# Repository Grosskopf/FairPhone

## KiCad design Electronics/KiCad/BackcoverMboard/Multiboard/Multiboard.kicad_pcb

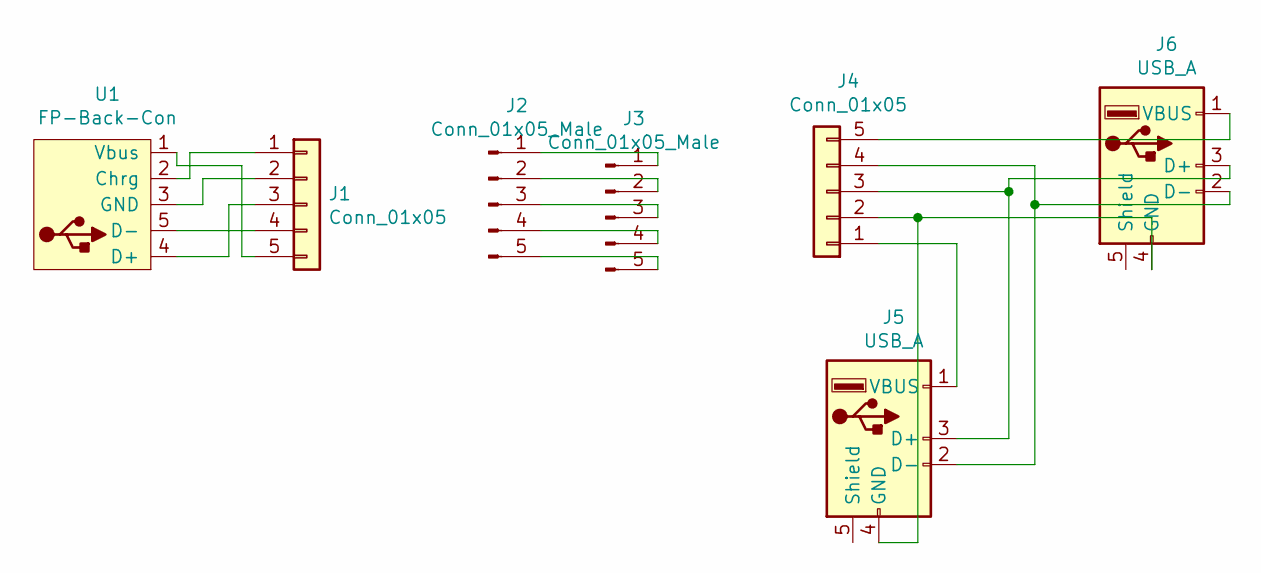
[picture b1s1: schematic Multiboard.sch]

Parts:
J1, J4: Conn_01x05; PinHeader_1x05_P2.54mm_Vertical
J2, J3: Conn_01x05_Male; Pad 01x05
J5: USB_A; usb-PCB
J6: USB_A; USB_A_Stewart_SS-52100-001_Horizontal
U1: FP-Back-Con; Fairphone-Back

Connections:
unnamed: J1.1, U1.2 (Chrg)
unnamed: J1.2, U1.3 (GND)
unnamed: J1.3, U1.4 (D+)
unnamed: J1.4, U1.5 (D-)
unnamed: J1.5, U1.1 (Vbus)
unnamed: J2.1, J3.1
unnamed: J2.2, J3.2
unnamed: J2.3, J3.3
unnamed: J2.4, J3.4
unnamed: J2.5, J3.5
unnamed: J4.1, J5.1 (VBUS)
unnamed: J4.2, J5.4 (GND), J6.4 (GND)
unnamed: J4.3, J5.3 (D+), J6.3 (D+)
unnamed: J4.4, J5.2 (D-), J6.2 (D-)
unnamed: J4.5, J6.1 (VBUS)

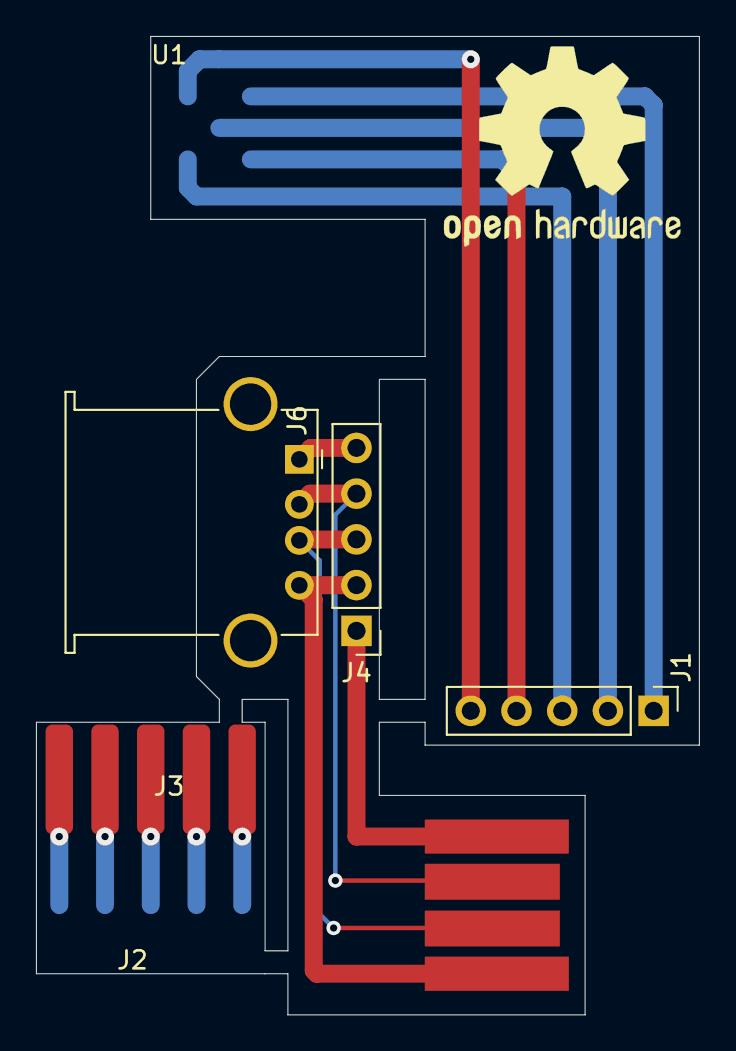
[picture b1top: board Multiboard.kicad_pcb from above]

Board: 2 copper layers, 36.8 x 54.4 mm, 7 parts (1 on the bottom side), 15 nets.

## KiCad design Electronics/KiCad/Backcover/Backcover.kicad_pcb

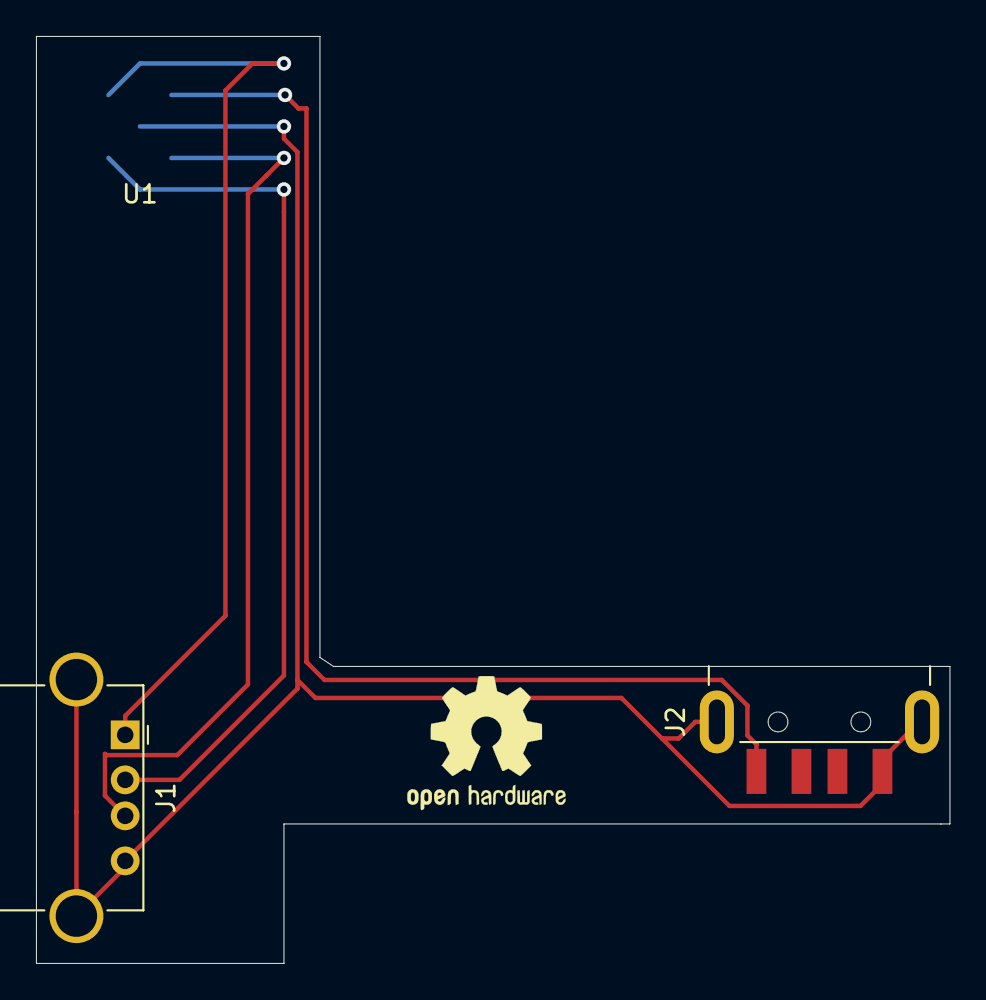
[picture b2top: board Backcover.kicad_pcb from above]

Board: 2 copper layers, 50.8 x 51.5 mm, 3 parts (0 on the bottom side), 5 nets.

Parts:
J1: USB_A; USB_A_Stewart_SS-52100-001_Horizontal
J2: USB_A; USB_A_CNCTech_1001-011-01101_Horizontal
U1: FP-Back-Con; Fairphone-Back

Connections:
GND: J1.4, J1.5, J2.4, J2.5
unnamed: J1.1, U1.vbus
unnamed: J1.2, U1.d+
unnamed: J1.3, U1.d-
unnamed: J2.1, U1.chrg

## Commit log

2019-09-30 Added My small Project, allows a Powerbank to be slid into the back of the Fairphone
2019-09-30 added gcode and an updated board for ideal positioning of my Intenso HC 20000
